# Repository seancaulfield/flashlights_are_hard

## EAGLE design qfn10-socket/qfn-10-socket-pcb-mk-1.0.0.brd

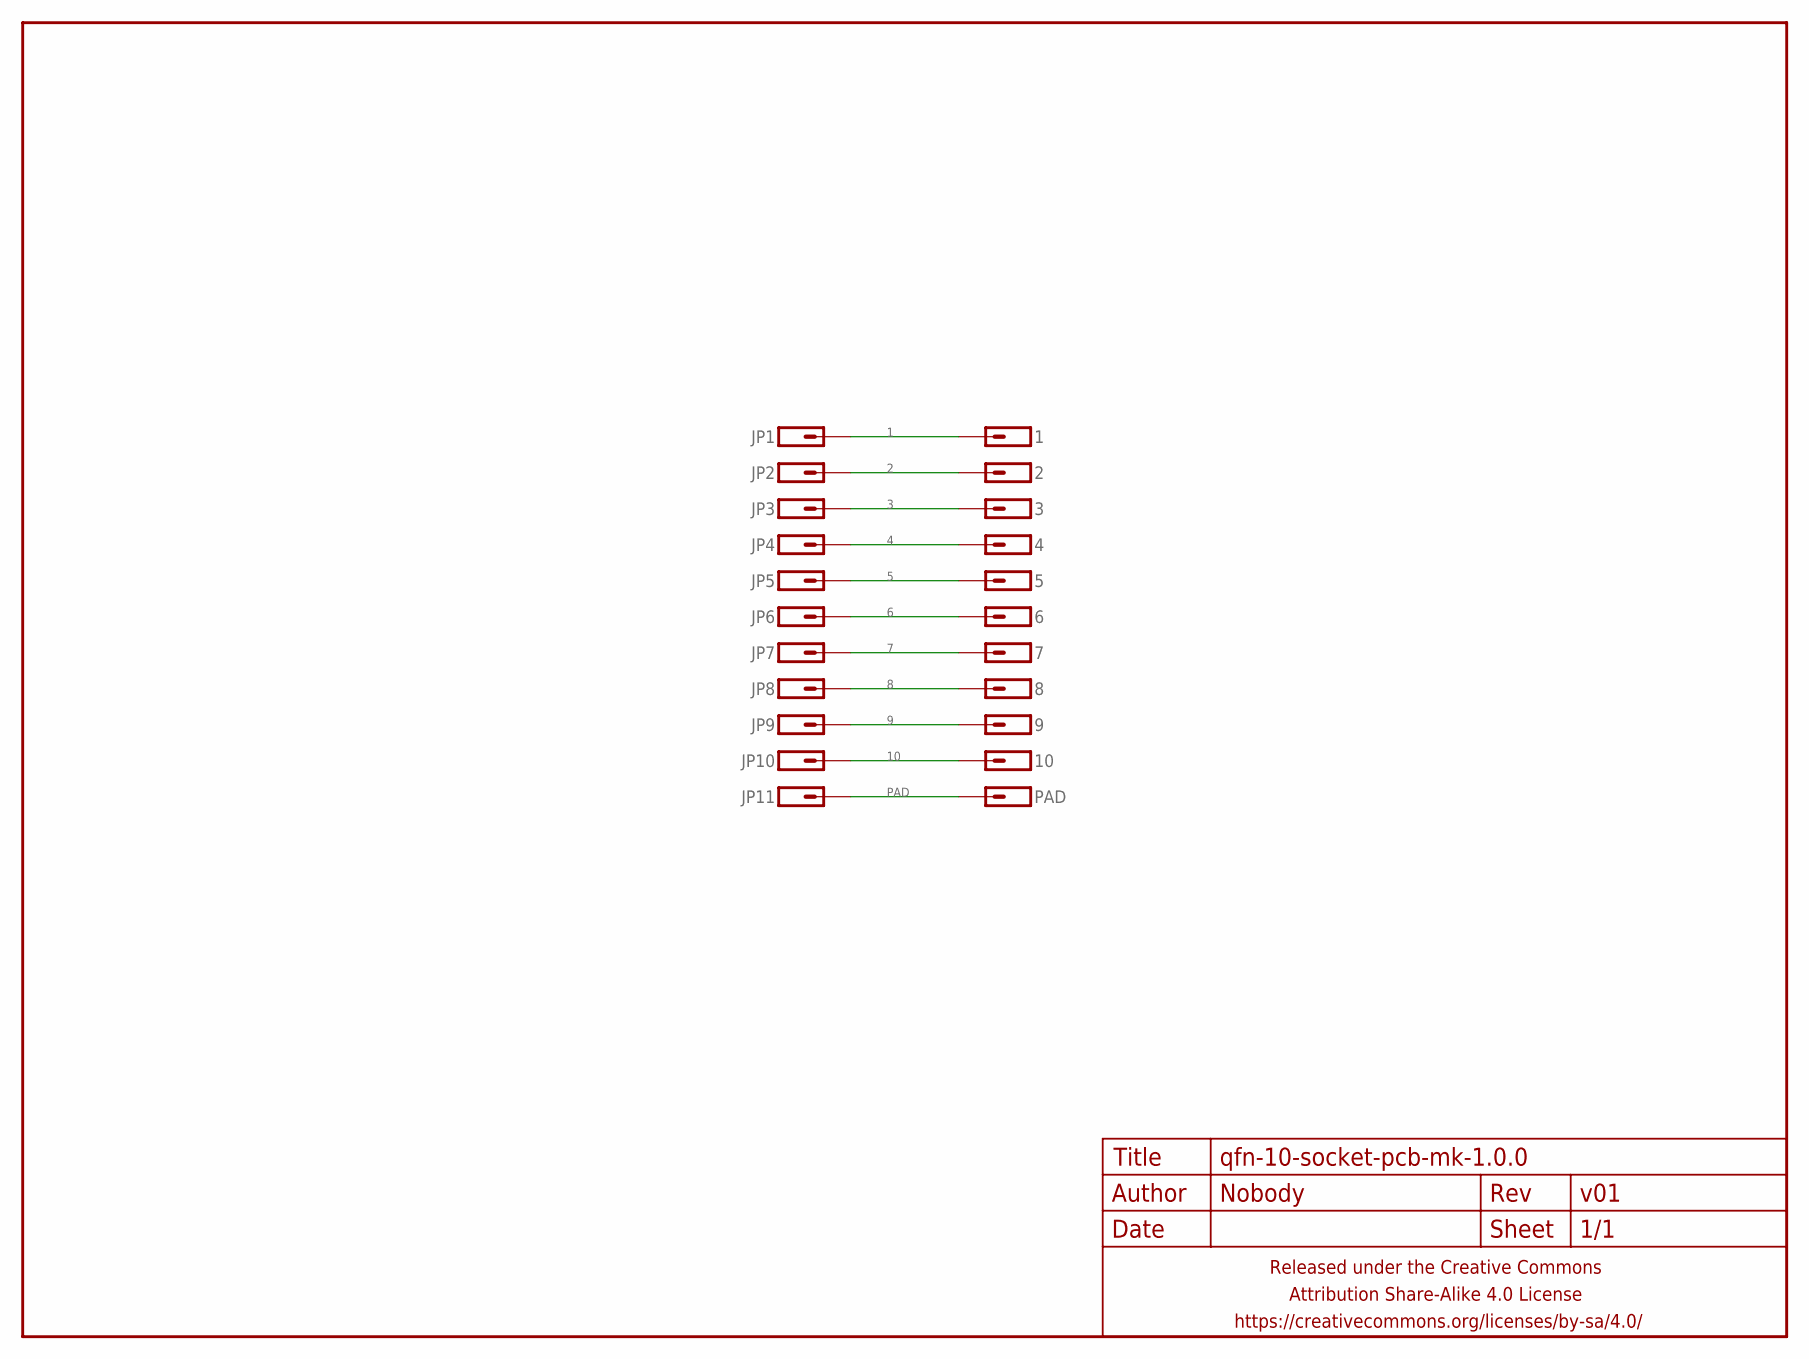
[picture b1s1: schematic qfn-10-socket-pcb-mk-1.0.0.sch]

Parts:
1, 2, 3, 4, 5, 6, 7, 8, 9, 10: M01PTH; 1X01
FRAME1: FRAME-LETTERNO_PACKAGE; DUMMY
JP1, JP2, JP3, JP4, JP5, JP6, JP7, JP8, JP9, JP10: M01PTH-0.4MM; 1X01-0.4MM
JP11: M01PTH; 1X01
PAD: M01PTH-3.3MM; 1X01-3.3MM

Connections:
1: 1.1, JP1.P$1
2: 2.1, JP2.P$1
3: 3.1, JP3.P$1
4: 4.1, JP4.P$1
5: 5.1, JP5.P$1
6: 6.1, JP6.P$1
7: 7.1, JP7.P$1
8: 8.1, JP8.P$1
9: 9.1, JP9.P$1
10: 10.1, JP10.P$1
PAD: JP11.1, PAD.P$1

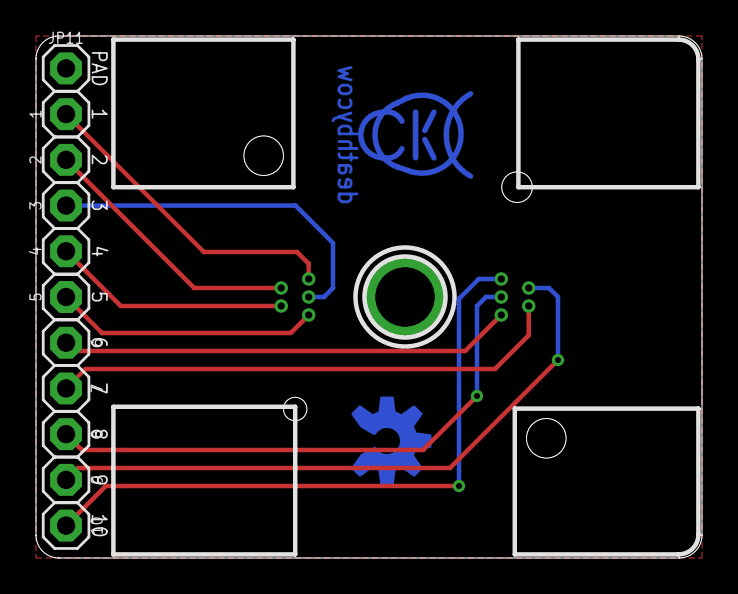
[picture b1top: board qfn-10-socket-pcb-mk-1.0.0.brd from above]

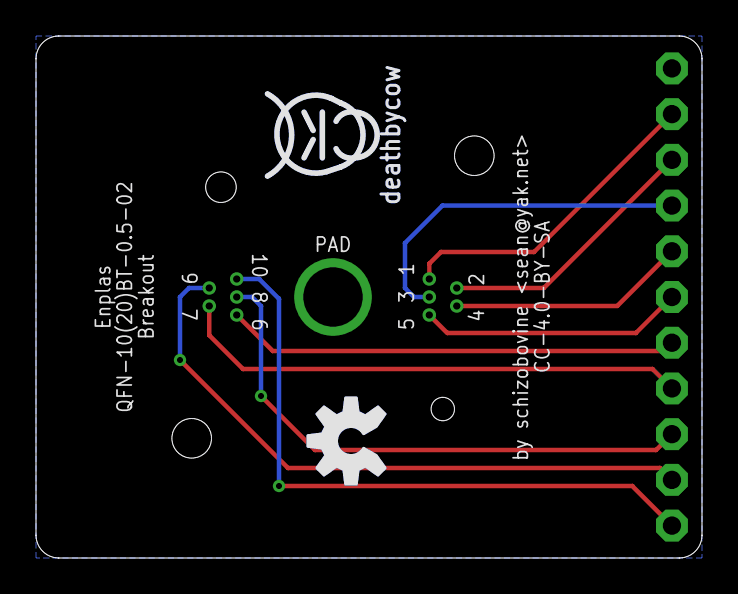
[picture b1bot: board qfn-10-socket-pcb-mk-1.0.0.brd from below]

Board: 2 copper layers, 37.0 x 29.0 mm, 25 parts (2 on the bottom side), 11 nets.

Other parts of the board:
U$1: COW_SMALL_METAL
U$2: OSHWLOGO_5MM_METAL

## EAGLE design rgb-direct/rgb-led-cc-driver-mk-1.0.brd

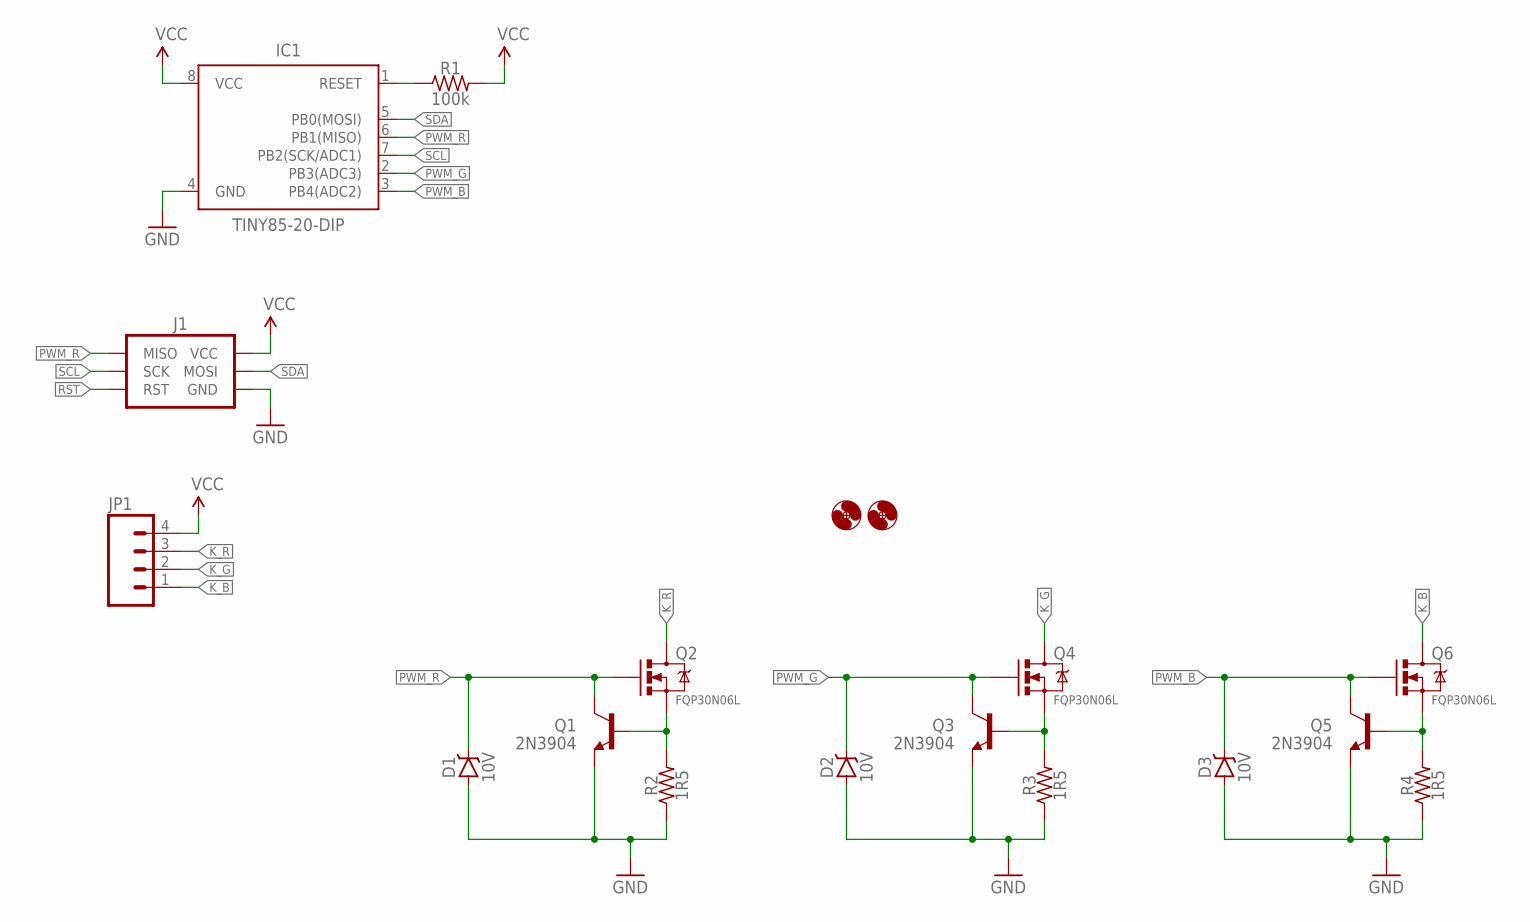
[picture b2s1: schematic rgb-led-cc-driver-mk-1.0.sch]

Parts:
D1, D2, D3: 10V; DIODE-ZENNER-10.16MM
H1, H2: HOLE#2; HOLE-#2
IC1: TINY85-20-DIP; DIP08
J1: AVR_SPI_PRG_6PTH_INLINE_I2C; AVR_ISP_INLINE_PTH_I2C
JP1: M04PTH; 1X04-PTH-VERT
Q1, Q3, Q5: 2N3904; TO-92-AMMO
Q2, Q4, Q6: FQP30N06L; TO220-THERMPAD
R1: 100k; RESISTOR-AXIAL-PTH-10.16MM
R2, R3, R4: 1R5; RESISTOR-AXIAL-PTH-10.16MM

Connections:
GND: D1.A, D2.A, D3.A, IC1.4 (GND), J1.GND, Q1.1 (E), Q3.1 (E), Q5.1 (E), R2.P$1 (1), R3.P$1 (1), R4.P$1 (1)
K_B: JP1.1, Q6.2@1 (D), Q6.2@2 (D)
K_G: JP1.2, Q4.2@1 (D), Q4.2@2 (D)
K_R: JP1.3, Q2.2@1 (D), Q2.2@2 (D)
unnamed: Q1.2 (B), Q2.3 (S), R2.P$2 (2)
unnamed: Q3.2 (B), Q4.3 (S), R3.P$2 (2)
unnamed: Q5.2 (B), Q6.3 (S), R4.P$2 (2)
PWM_B: D3.K (C), IC1.3 (PB4(ADC2)), Q5.3 (C), Q6.1 (G)
PWM_G: D2.K (C), IC1.2 (PB3(ADC3)), Q3.3 (C), Q4.1 (G)
PWM_R: D1.K (C), IC1.6 (PB1(MISO)), J1.MISO, Q1.3 (C), Q2.1 (G)
RST: IC1.1 (RESET), J1.RESET (RST), R1.P$1 (1)
SCL: IC1.7 (PB2(SCK/ADC1)), J1.SCK
SDA: IC1.5 (PB0(MOSI)), J1.MOSI
VCC: IC1.8 (VCC), J1.VCC, JP1.4, R1.P$2 (2)

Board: 2 copper layers, 18 parts (0 on the bottom side), 14 nets, no tracks yet.

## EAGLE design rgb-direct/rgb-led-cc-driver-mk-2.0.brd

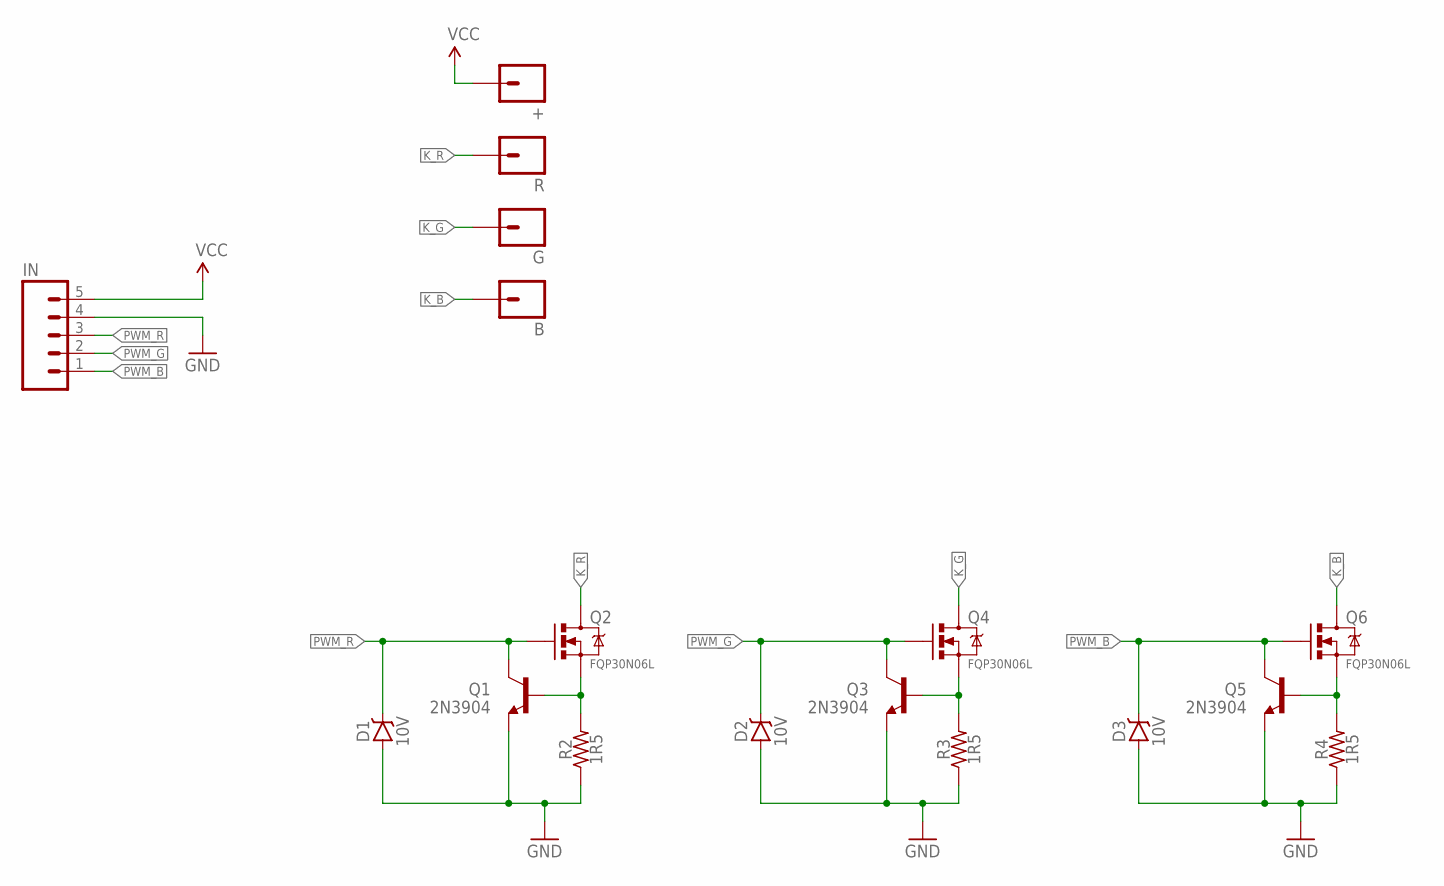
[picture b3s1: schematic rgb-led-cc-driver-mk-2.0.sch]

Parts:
+: M01PTH_2MM; 1X01_2MM
B: M01PTH_2MM; 1X01_2MM
D1, D2, D3: 10V; DIODE-ZENNER-7.62MM
G: M01PTH_2MM; 1X01_2MM
IN: M05PTH; 1X05
Q1, Q3, Q5: 2N3904; TO-92-AMMO
Q2, Q4, Q6: FQP30N06L; TO220-THERMPAD-OFFSETPADS
R: M01PTH_2MM; 1X01_2MM
R2, R3, R4: 1R5; RESISTOR-AXIAL-PTH-10.16MM

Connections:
GND: D1.A, D2.A, D3.A, IN.4, Q1.1 (E), Q3.1 (E), Q5.1 (E), R2.P$1 (1), R3.P$1 (1), R4.P$1 (1)
K_B: B.1, Q6.2@2 (D)
K_G: G.1, Q4.2@2 (D)
K_R: Q2.2@2 (D), R.1
unnamed: Q1.2 (B), Q2.3 (S), R2.P$2 (2)
unnamed: Q3.2 (B), Q4.3 (S), R3.P$2 (2)
unnamed: Q5.2 (B), Q6.3 (S), R4.P$2 (2)
PWM_B: D3.K (C), IN.1, Q5.3 (C), Q6.1 (G)
PWM_G: D2.K (C), IN.2, Q3.3 (C), Q4.1 (G)
PWM_R: D1.K (C), IN.3, Q1.3 (C), Q2.1 (G)
VCC: +.1, IN.5

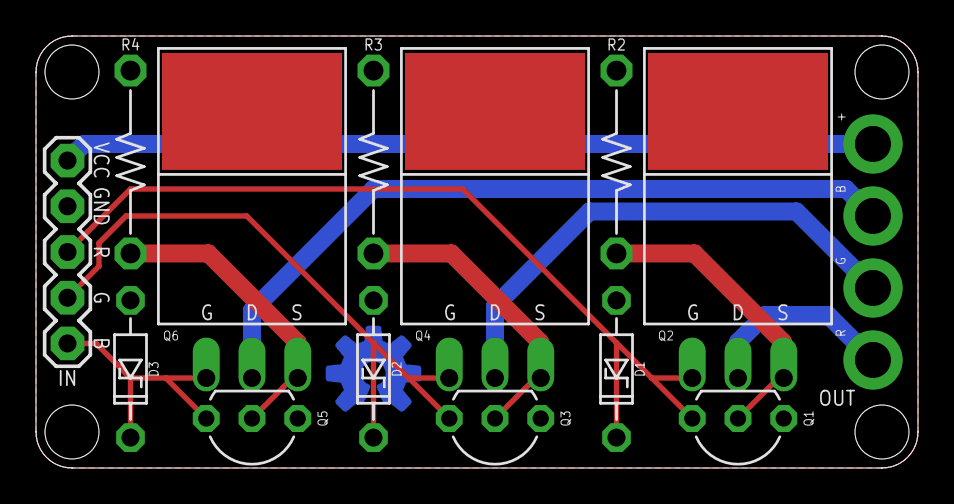
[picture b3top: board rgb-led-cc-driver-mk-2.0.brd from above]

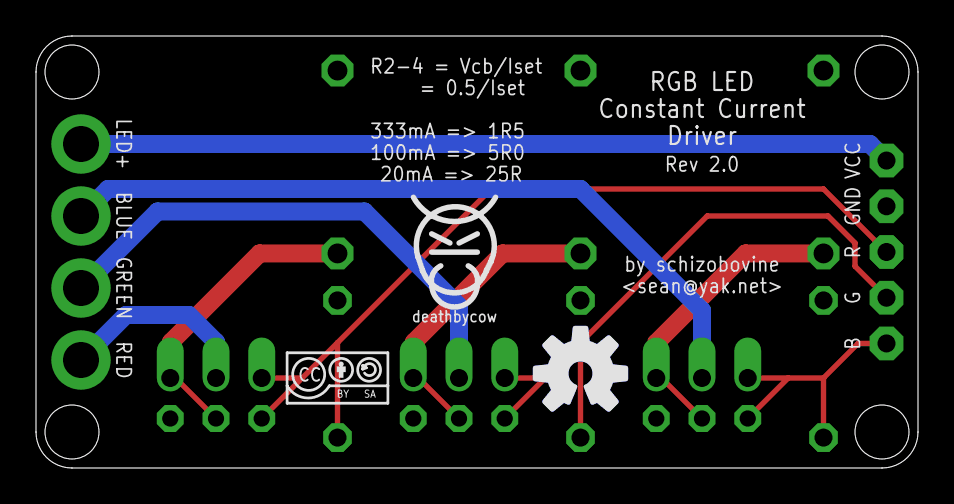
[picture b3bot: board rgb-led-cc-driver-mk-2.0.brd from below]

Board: 2 copper layers, 49.0 x 24.0 mm, 20 parts (2 on the bottom side), 11 nets.

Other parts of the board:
U$1: CC-BY-SA-4.0-NO-URL
U$2: COW_SMALL
U$3: OSHWLOGO_BOT_0.2_A

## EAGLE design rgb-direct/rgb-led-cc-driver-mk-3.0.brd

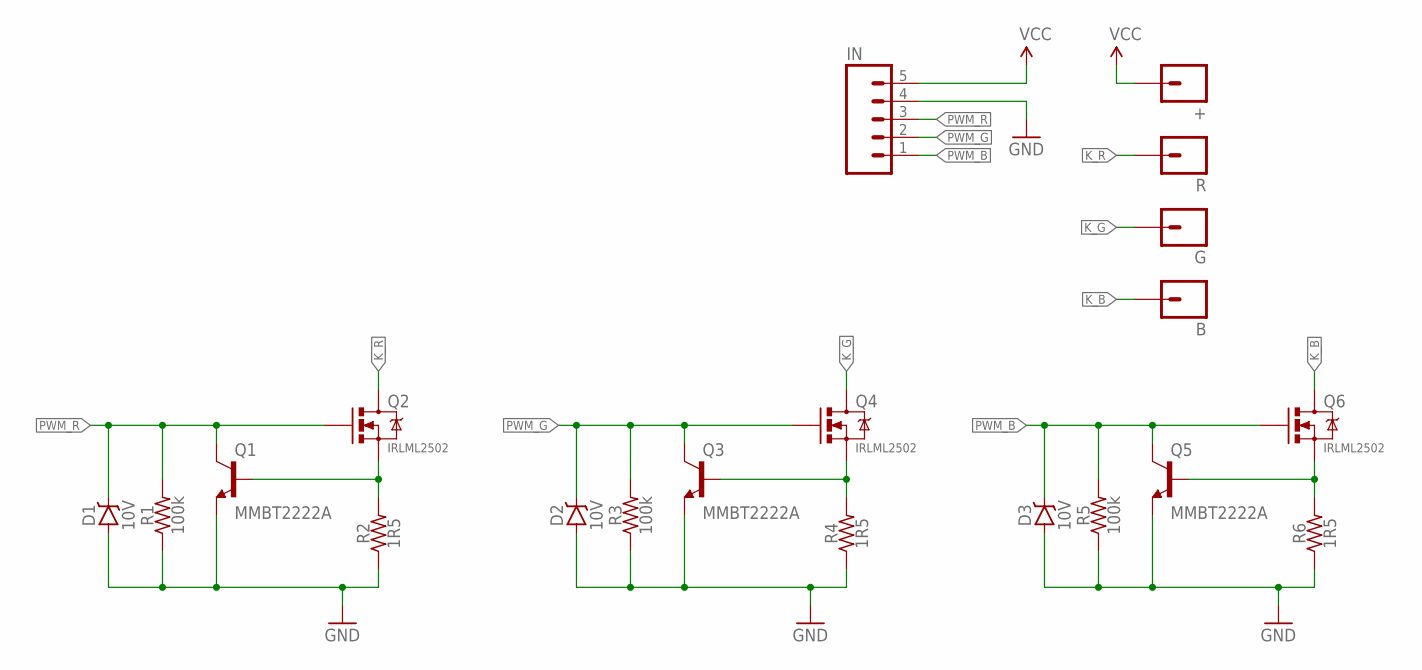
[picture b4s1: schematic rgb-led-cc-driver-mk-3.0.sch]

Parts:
+: M01PTH_2MM; 1X01_2MM
B: M01PTH_2MM; 1X01_2MM
D1, D2, D3: 10V; SOD123-ZENER
G: M01PTH_2MM; 1X01_2MM
IN: M05PTH; 1X05
Q1, Q3, Q5: MMBT2222A; SOT23
Q2, Q4, Q6: IRLML2502; SOT23
R: M01PTH_2MM; 1X01_2MM
R1, R3, R5: 100k; R0805
R2, R4, R6: 1R5; R1206

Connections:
GND: D1.A, D2.A, D3.A, IN.4, Q1.2 (E), Q3.2 (E), Q5.2 (E), R1.1, R2.1, R3.1, R4.1, R5.1, R6.1
K_B: B.1, Q6.3 (D)
K_G: G.1, Q4.3 (D)
K_R: Q2.3 (D), R.1
unnamed: Q1.1 (B), Q2.2 (S), R2.2
unnamed: Q3.1 (B), Q4.2 (S), R4.2
unnamed: Q5.1 (B), Q6.2 (S), R6.2
PWM_B: D3.C, IN.1, Q5.3 (C), Q6.1 (G), R5.2
PWM_G: D2.C, IN.2, Q3.3 (C), Q4.1 (G), R3.2
PWM_R: D1.C, IN.3, Q1.3 (C), Q2.1 (G), R1.2
VCC: +.1, IN.5

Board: 2 copper layers, 23 parts (2 on the bottom side), 11 nets, no tracks yet.

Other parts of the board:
U$1: CC-BY-SA-4.0-NO-URL
U$2: COW_SMALL
U$3: OSHWLOGO_BOT_0.2_A

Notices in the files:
parts and their libraries:
a_parts: Released under the Creative Commons Attribution Share-Alike 4.0 License
a_parts: https://creativecommons.org/licenses/by-sa/4.0
a_parts: Released under the Creative Commons
